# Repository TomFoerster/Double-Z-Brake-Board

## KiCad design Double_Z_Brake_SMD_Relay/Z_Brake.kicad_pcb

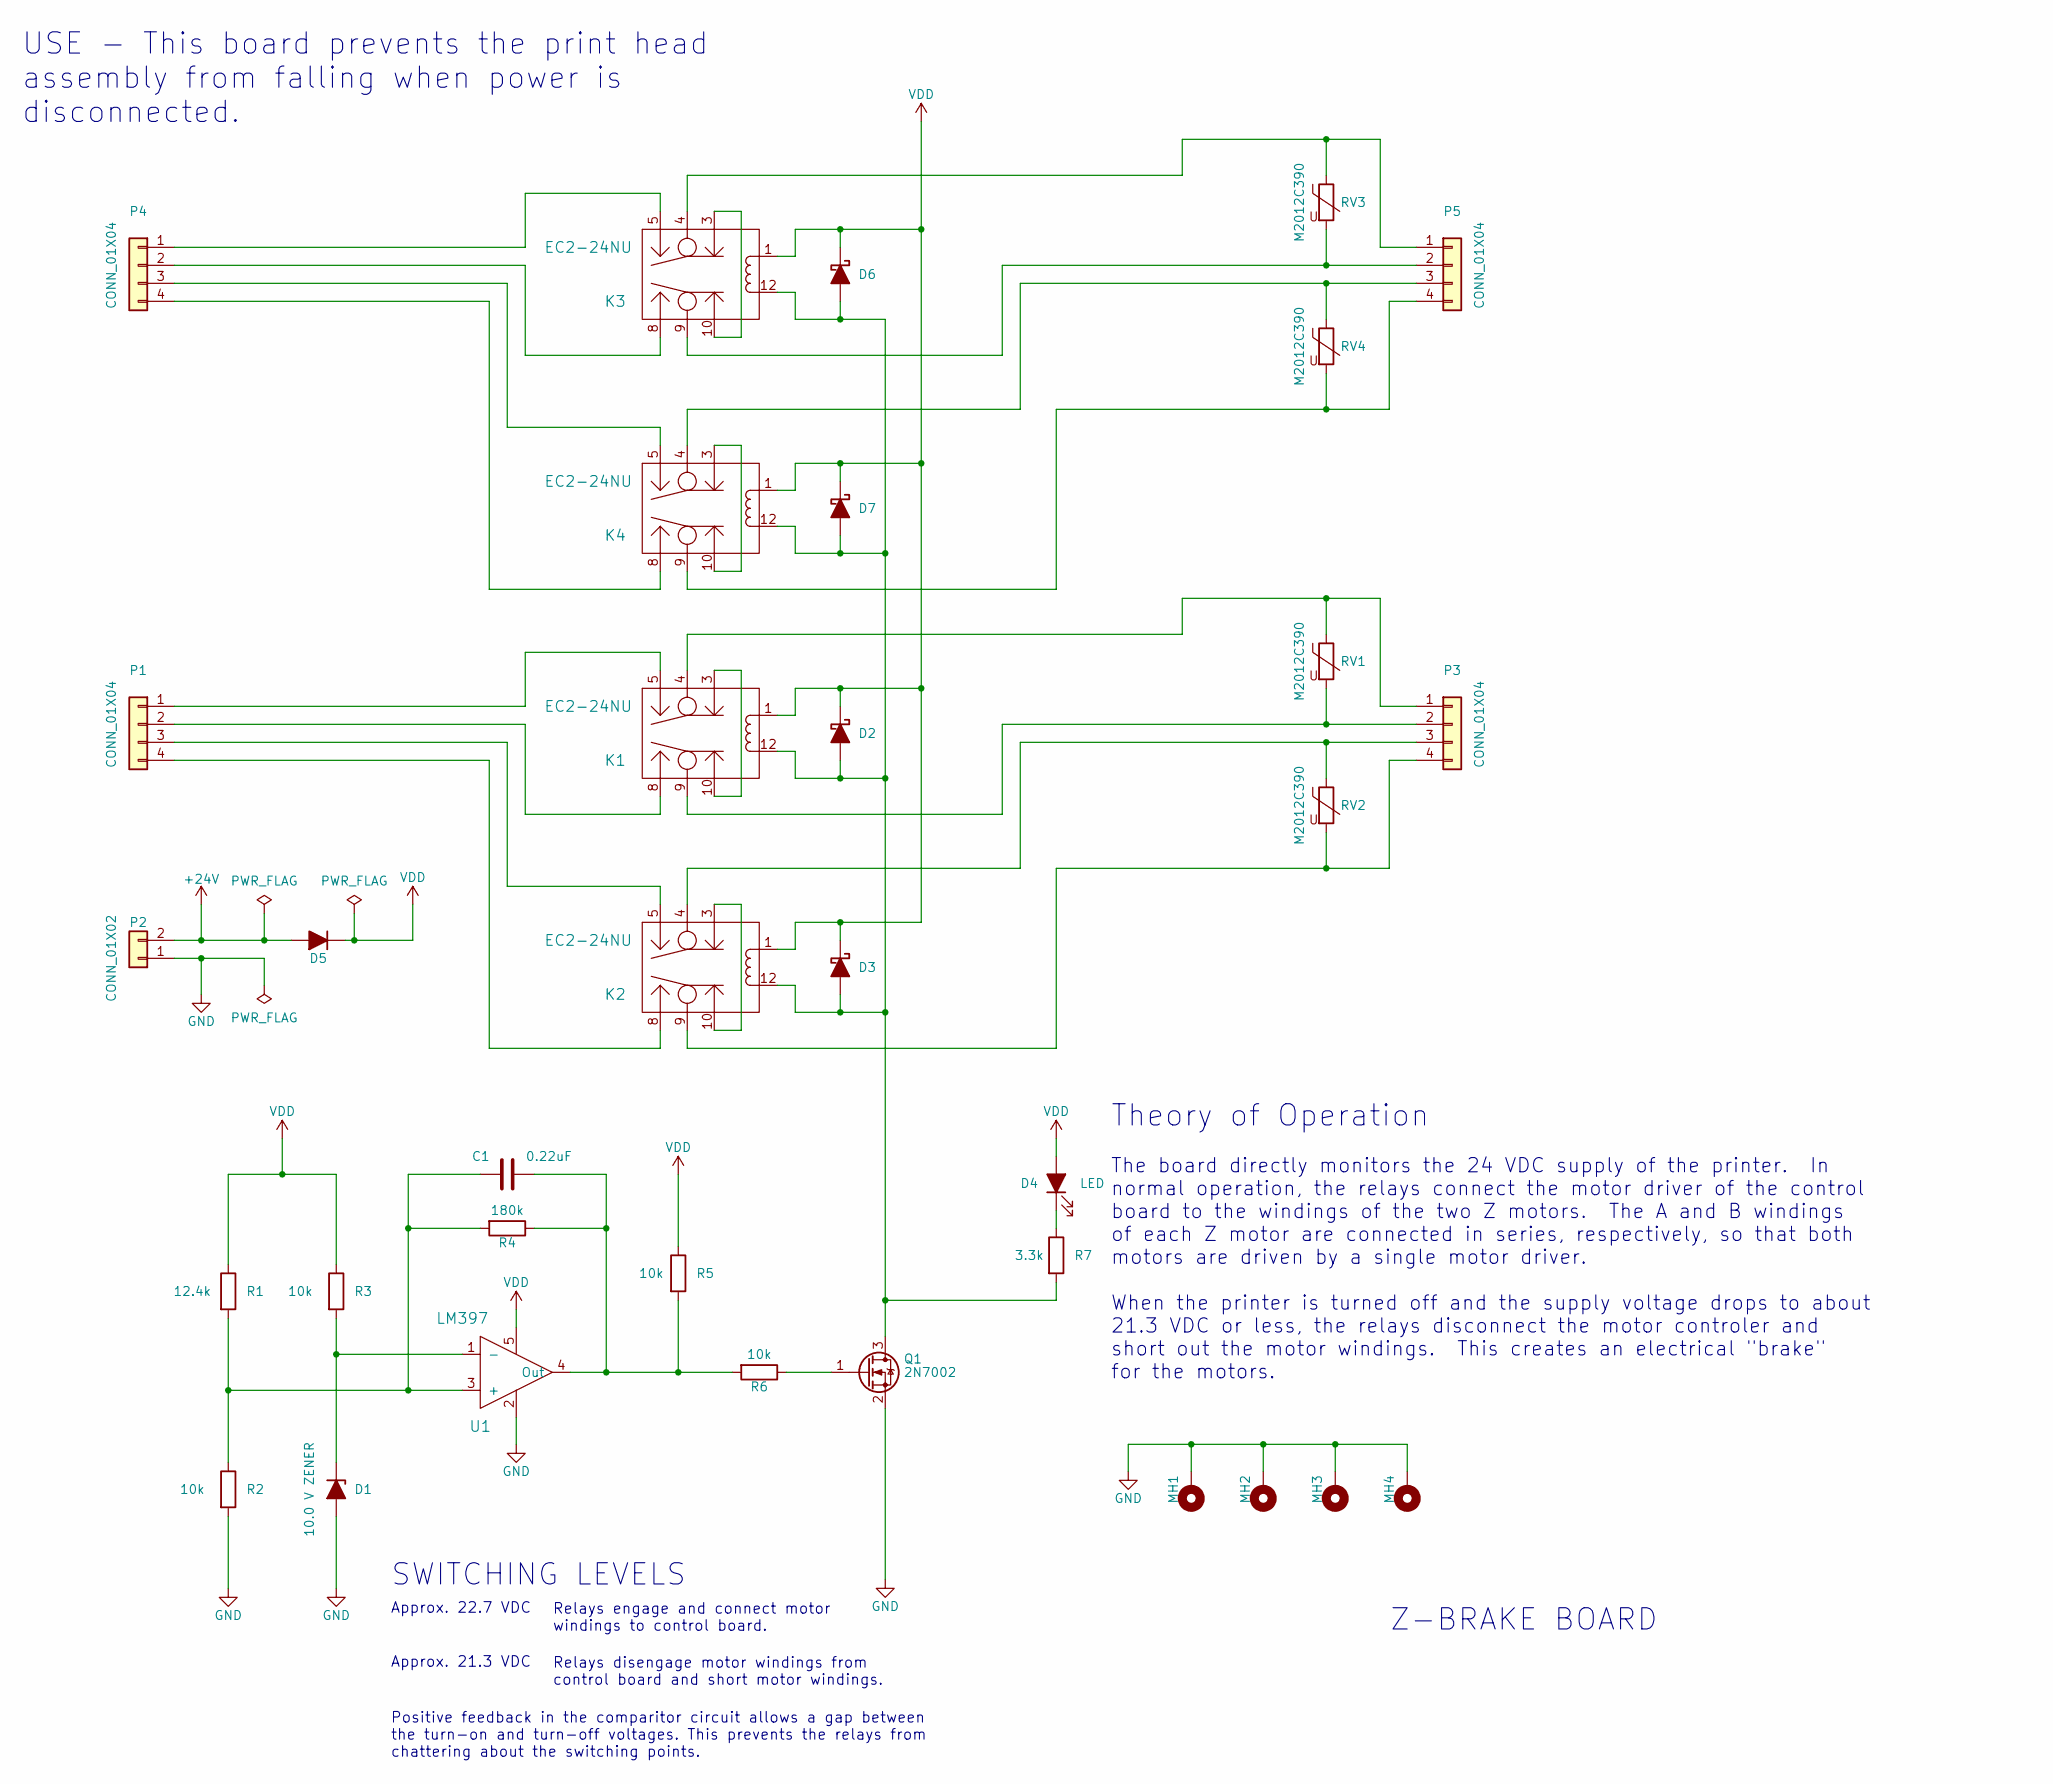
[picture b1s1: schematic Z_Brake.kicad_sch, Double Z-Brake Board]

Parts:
C1: 0.22uF; C_0603_1608Metric_Pad1.08x0.95mm_HandSolder; MPN CL10B224KB8VPNC
D1: 10.0 V ZENER; D_SMA_Handsoldering; MPN SMAZ10-13-F
D2, D3, D6, D7: D_Schottky_ALT; D_SOD-123; MPN BAT48ZFILM
D4: LED; LED_0603_1608Metric_Pad1.05x0.95mm_HandSolder; MPN LTST-C190YKT
D5: D_ALT; D_SMA_Handsoldering; MPN CDBA340-HF
K1, K2, K3, K4: EC2-24NU; Relay_DPDT_Kemet_EE2_NU; MPN EC2-24NU
MH1, MH2, MH3, MH4: CONN_01X01; MountingHole_2.5mm_Pad
P1, P3, P4, P5: CONN_01X04; Molex-70543-0038-0-0-MFG; MPN 0705430003
P2: CONN_01X02; MOLEX_0705430001; MPN 0705430001
Q1: 2N7002; SOT-23_Handsoldering; MPN 2N7002 TR PBFREE
R1: 12.4k; R_0603_1608Metric_Pad0.98x0.95mm_HandSolder; MPN RC0603FR-0712K4L
R2, R3, R5, R6: 10k; R_0603_1608Metric_Pad0.98x0.95mm_HandSolder; MPN RC0603FR-0710KL
R4: 180k; R_0603_1608Metric_Pad0.98x0.95mm_HandSolder; MPN RC0603FR-07180KL
R7: 3.3k; R_0603_1608Metric_Pad0.98x0.95mm_HandSolder; MPN RC0603FR-073K3L
RV1, RV2, RV3, RV4: M2012C390; R_0805_2012Metric_Pad1.20x1.40mm_HandSolder; MPN AVR-M2012C390KT6AB
U1: LM397; SOT-23-5_HandSoldering; MPN LM397MF/NOPB

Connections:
+24V: D5.2 (A), P2.2
GND: D1.2 (A), MH1.1, MH2.1, MH3.1, MH4.1, P2.1, Q1.2 (S), R2.2, U1.2
unnamed: D1.1 (K), R3.2, U1.1 (-)
unnamed: D2.2 (A), D3.2 (A), D6.2 (A), D7.2 (A), K1.12, K2.12, K3.12, K4.12, Q1.3 (D), R7.2
unnamed: D4.1 (K), R7.1
unnamed: K1.3, K1.10
unnamed: K2.3, K2.10
unnamed: K3.3, K3.10
unnamed: K4.3, K4.10
unnamed: K1.5, P1.1
unnamed: K1.8, P1.2
unnamed: K2.5, P1.3
unnamed: K2.8, P1.4
unnamed: K1.4, P3.1, RV1.1
unnamed: K1.9, P3.2, RV1.2
unnamed: K2.4, P3.3, RV2.1
unnamed: K2.9, P3.4, RV2.2
unnamed: K3.5, P4.1
unnamed: K3.8, P4.2
unnamed: K4.5, P4.3
unnamed: K4.8, P4.4
unnamed: K3.4, P5.1, RV3.1
unnamed: K3.9, P5.2, RV3.2
unnamed: K4.4, P5.3, RV4.1
unnamed: K4.9, P5.4, RV4.2
unnamed: Q1.1 (G), R6.1
unnamed: C1.2, R1.2, R2.1, R4.2, U1.3 (+)
unnamed: C1.1, R4.1, R5.2, R6.2, U1.4 (Out)
VDD: D2.1 (K), D3.1 (K), D4.2 (A), D5.1 (K), D6.1 (K), D7.1 (K), K1.1, K2.1, K3.1, K4.1, R1.1, R3.1, R5.1, U1.5

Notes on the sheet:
Theory of Operation
SWITCHING LEVELS
Relays engage and connect motor windings to control board.
Z-BRAKE BOARD
Relays disengage motor windings from control board and short motor windings.
USE - This board prevents the print head assembly from falling when power is disconnected.
The board directly monitors the 24 VDC supply of the printer. In normal operation, the relays connect the motor driver of the control board to the windings of the two Z motors. The A and B windings of each Z motor are connected in series, respectively, so that both motors are driven by a single mot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
Approx. 21.3 VDC
Approx. 22.7 VDC
Positive feedback in the comparitor circuit allows a gap between the turn-on and turn-off voltages. This prevents the relays from chattering about the switching points.

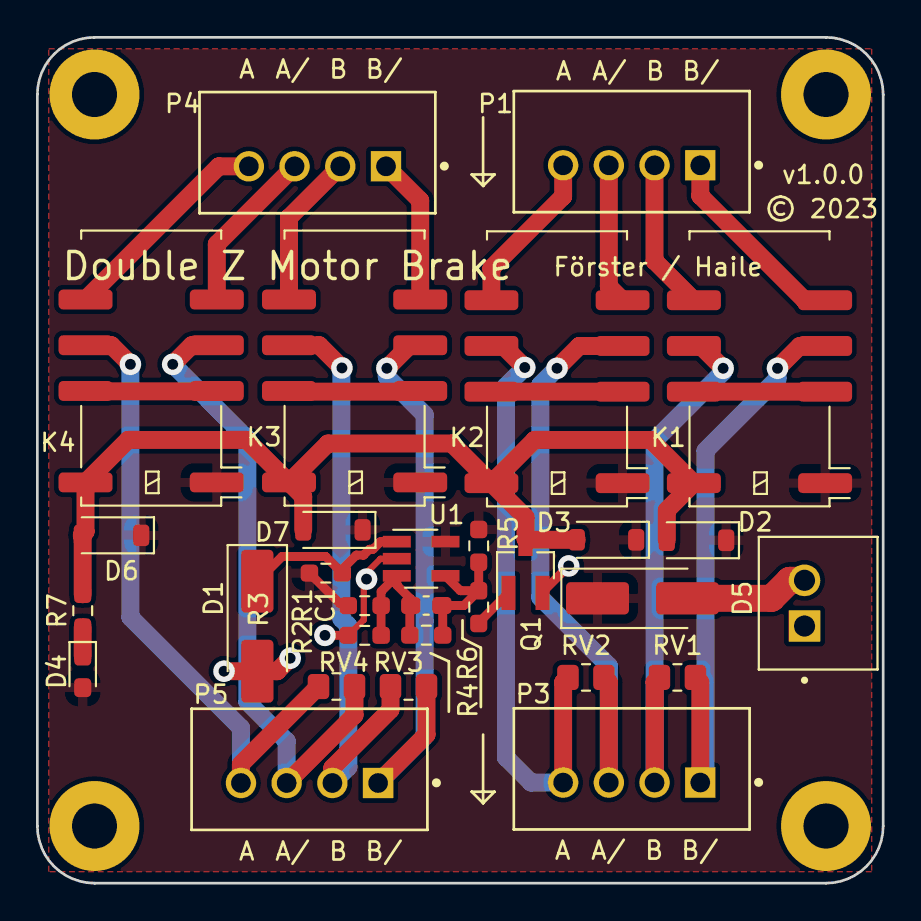
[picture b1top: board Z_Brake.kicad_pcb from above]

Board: 2 copper layers, 47.0 x 47.0 mm, 34 parts (0 on the bottom side), 29 nets.

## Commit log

2023-03-20 Changed Z Brake board to feature 2 motors
2025-03-02 Added ibom

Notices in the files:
Double_Z_Brake_SMD_Relay/Z_Brake.kicad_pcb:
© 2023
